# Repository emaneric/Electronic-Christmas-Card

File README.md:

# Electronic-Christmas-Card
A christmas card made from a PCB with a LED display, buttons, and buzzer.

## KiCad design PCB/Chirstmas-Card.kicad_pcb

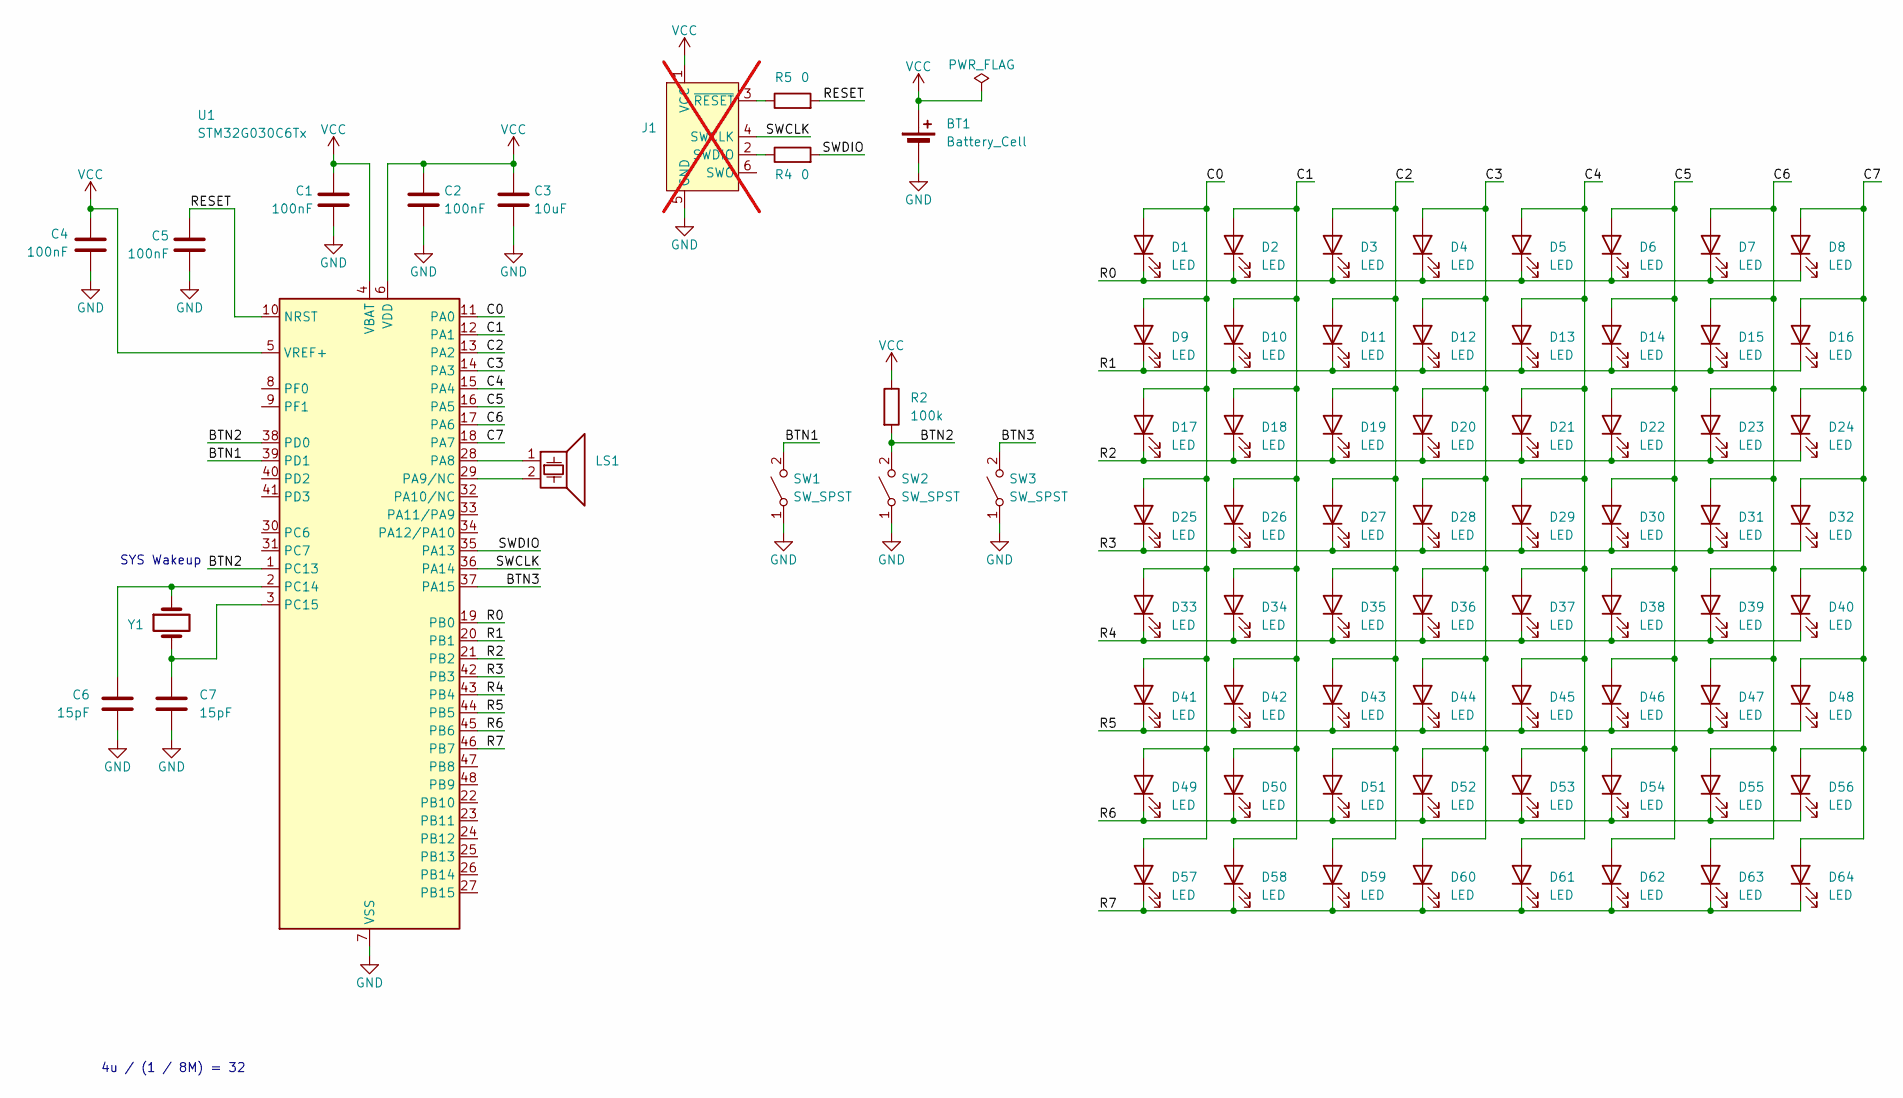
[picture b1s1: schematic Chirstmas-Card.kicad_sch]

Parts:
BT1: Battery_Cell; CR2032-BS-6-1; MPN CR2032-BS-6-1; JLC C70377
C1, C2, C4, C5: 100nF; C_0402_1005Metric; MPN CC0402KRX7R9BB104; JLC C131394
C3: 10uF; C_0603_1608Metric; MPN CL10A106MA8NRNC; JLC C96446
C6, C7: 15pF; C_0402_1005Metric; MPN 0402CG150J500NT; JLC C1548
D1, D2, D3, D4, D5, D6, D7, D8, D9, D10, D11, D12, D13, D14, D15, D16, D17, D18, D19, D20, D21, D22, D23, D24, D25, D26, D27, D28, D29, D30, D31, D32, D33, D34, D35, D36, D37, D38, D39, D40, D41, D42, D43, D44, D45, D46, D47, D48, D49, D50, D51, D52, D53, D54, D55, D56, D57, D58, D59, D60, D61, D62, D63, D64: LED; MHT151WDT; MPN MHT151WDT; JLC C401114
J1: Conn_ARM_SWD_TagConnect_TC2030-NL; Tag-Connect_TC2030-IDC-NL_2x03_P1.27mm_Vertical; not fitted
LS1: Speaker_Crystal; FUET-1230; MPN FUET-1230; JLC C391037
R2: 100k; R_0603_1608Metric; MPN 0402WGF1003TCE; JLC C25741
R4, R5: 0; R_0603_1608Metric; MPN 0402WGF1003TCE; JLC C25741
SW1, SW2, SW3: SW_SPST; KH-6X6X5H-STM; MPN KH-6X6X5H-STM; JLC C2837531
U1: STM32G030C6Tx; LQFP-48_7x7mm_P0.5mm; MPN STM32G030C6T6; JLC C529328
Y1: Crystal; Crystal_SMD_3215-2Pin_3.2x1.5mm; MPN Q13FC1350000400; JLC C32346

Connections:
/BTN1: SW1.2 (B), U1.39 (PD1)
/BTN2: R2.2, SW2.2 (B), U1.1 (PC13), U1.38 (PD0)
/BTN3: SW3.2 (B), U1.37 (PA15)
/C0: D1.2 (A), D9.2 (A), D17.2 (A), D25.2 (A), D33.2 (A), D41.2 (A), D49.2 (A), D57.2 (A), U1.11 (PA0)
/C1: D2.2 (A), D10.2 (A), D18.2 (A), D26.2 (A), D34.2 (A), D42.2 (A), D50.2 (A), D58.2 (A), U1.12 (PA1)
/C2: D3.2 (A), D11.2 (A), D19.2 (A), D27.2 (A), D35.2 (A), D43.2 (A), D51.2 (A), D59.2 (A), U1.13 (PA2)
/C3: D4.2 (A), D12.2 (A), D20.2 (A), D28.2 (A), D36.2 (A), D44.2 (A), D52.2 (A), D60.2 (A), U1.14 (PA3)
/C4: D5.2 (A), D13.2 (A), D21.2 (A), D29.2 (A), D37.2 (A), D45.2 (A), D53.2 (A), D61.2 (A), U1.15 (PA4)
/C5: D6.2 (A), D14.2 (A), D22.2 (A), D30.2 (A), D38.2 (A), D46.2 (A), D54.2 (A), D62.2 (A), U1.16 (PA5)
/C6: D7.2 (A), D15.2 (A), D23.2 (A), D31.2 (A), D39.2 (A), D47.2 (A), D55.2 (A), D63.2 (A), U1.17 (PA6)
/C7: D8.2 (A), D16.2 (A), D24.2 (A), D32.2 (A), D40.2 (A), D48.2 (A), D56.2 (A), D64.2 (A), U1.18 (PA7)
/R0: D1.1 (K), D2.1 (K), D3.1 (K), D4.1 (K), D5.1 (K), D6.1 (K), D7.1 (K), D8.1 (K), U1.19 (PB0)
/R1: D9.1 (K), D10.1 (K), D11.1 (K), D12.1 (K), D13.1 (K), D14.1 (K), D15.1 (K), D16.1 (K), U1.20 (PB1)
/R2: D17.1 (K), D18.1 (K), D19.1 (K), D20.1 (K), D21.1 (K), D22.1 (K), D23.1 (K), D24.1 (K), U1.21 (PB2)
/R3: D25.1 (K), D26.1 (K), D27.1 (K), D28.1 (K), D29.1 (K), D30.1 (K), D31.1 (K), D32.1 (K), U1.42 (PB3)
/R4: D33.1 (K), D34.1 (K), D35.1 (K), D36.1 (K), D37.1 (K), D38.1 (K), D39.1 (K), D40.1 (K), U1.43 (PB4)
/R5: D41.1 (K), D42.1 (K), D43.1 (K), D44.1 (K), D45.1 (K), D46.1 (K), D47.1 (K), D48.1 (K), U1.44 (PB5)
/R6: D49.1 (K), D50.1 (K), D51.1 (K), D52.1 (K), D53.1 (K), D54.1 (K), D55.1 (K), D56.1 (K), U1.45 (PB6)
/R7: D57.1 (K), D58.1 (K), D59.1 (K), D60.1 (K), D61.1 (K), D62.1 (K), D63.1 (K), D64.1 (K), U1.46 (PB7)
/RESET: C5.1, R5.2, U1.10 (NRST)
/SWCLK: J1.4 (SWCLK), U1.36 (PA14)
/SWDIO: R4.2, U1.35 (PA13)
GND: BT1.2 (-), C1.2, C2.2, C3.2, C4.2, C5.2, C6.2, C7.2, J1.5 (GND), SW1.1 (A), SW2.1 (A), SW3.1 (A), U1.7 (VSS)
unnamed: J1.2 (SWDIO), R4.1
unnamed: J1.3 (~RESET), R5.1
unnamed: LS1.1, U1.28 (PA8)
unnamed: LS1.2, U1.29 (PA9/NC)
unnamed: C6.1, U1.2 (PC14), Y1.1
unnamed: C7.1, U1.3 (PC15), Y1.2
VCC: BT1.1 (+), C1.1, C2.1, C3.1, C4.1, J1.1 (VCC), R2.1, U1.4 (VBAT), U1.5 (VREF+), U1.6 (VDD)

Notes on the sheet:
SYS Wakeup
4u / (1 / 8M) = 32

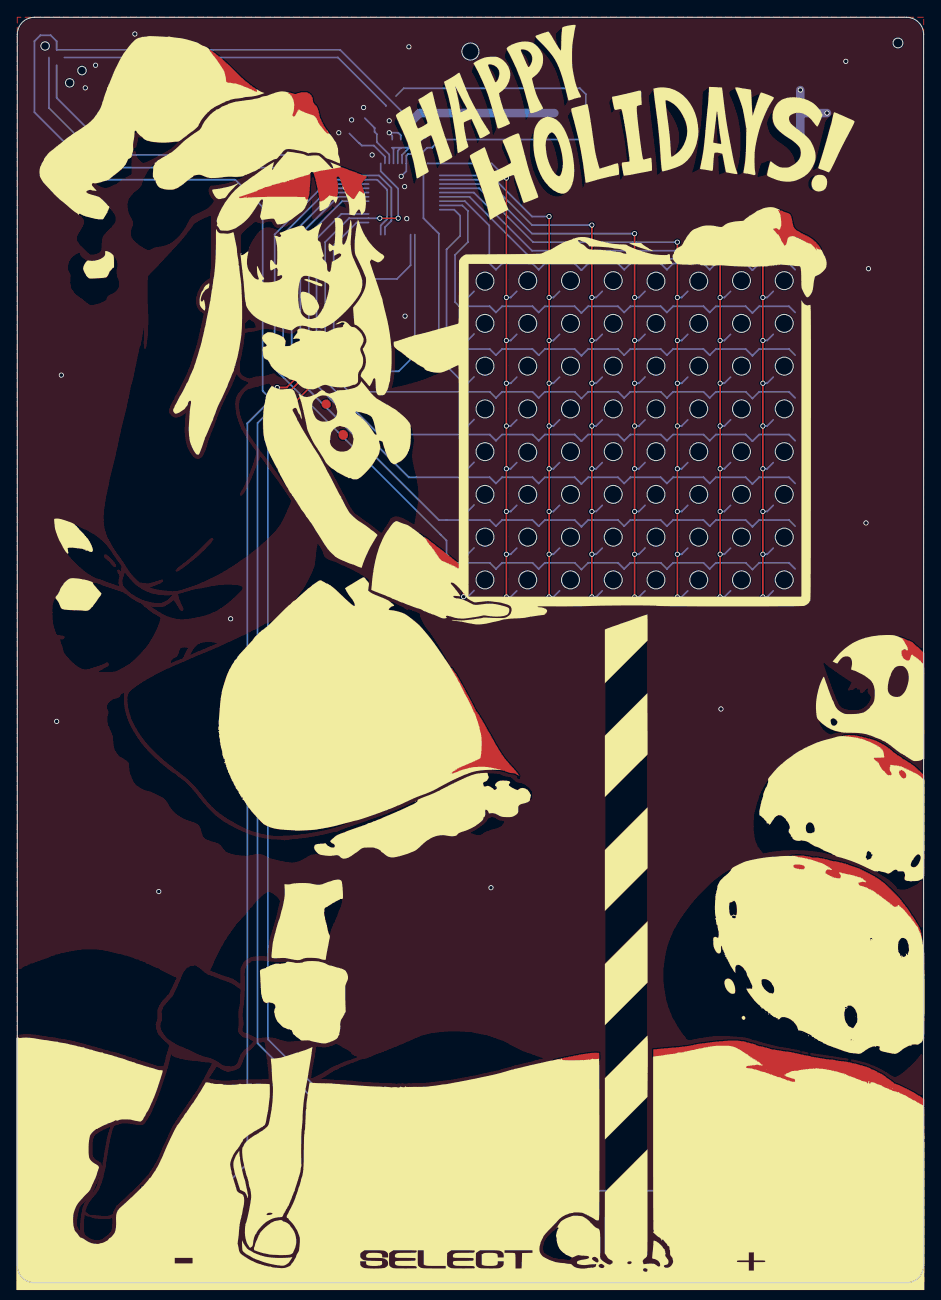
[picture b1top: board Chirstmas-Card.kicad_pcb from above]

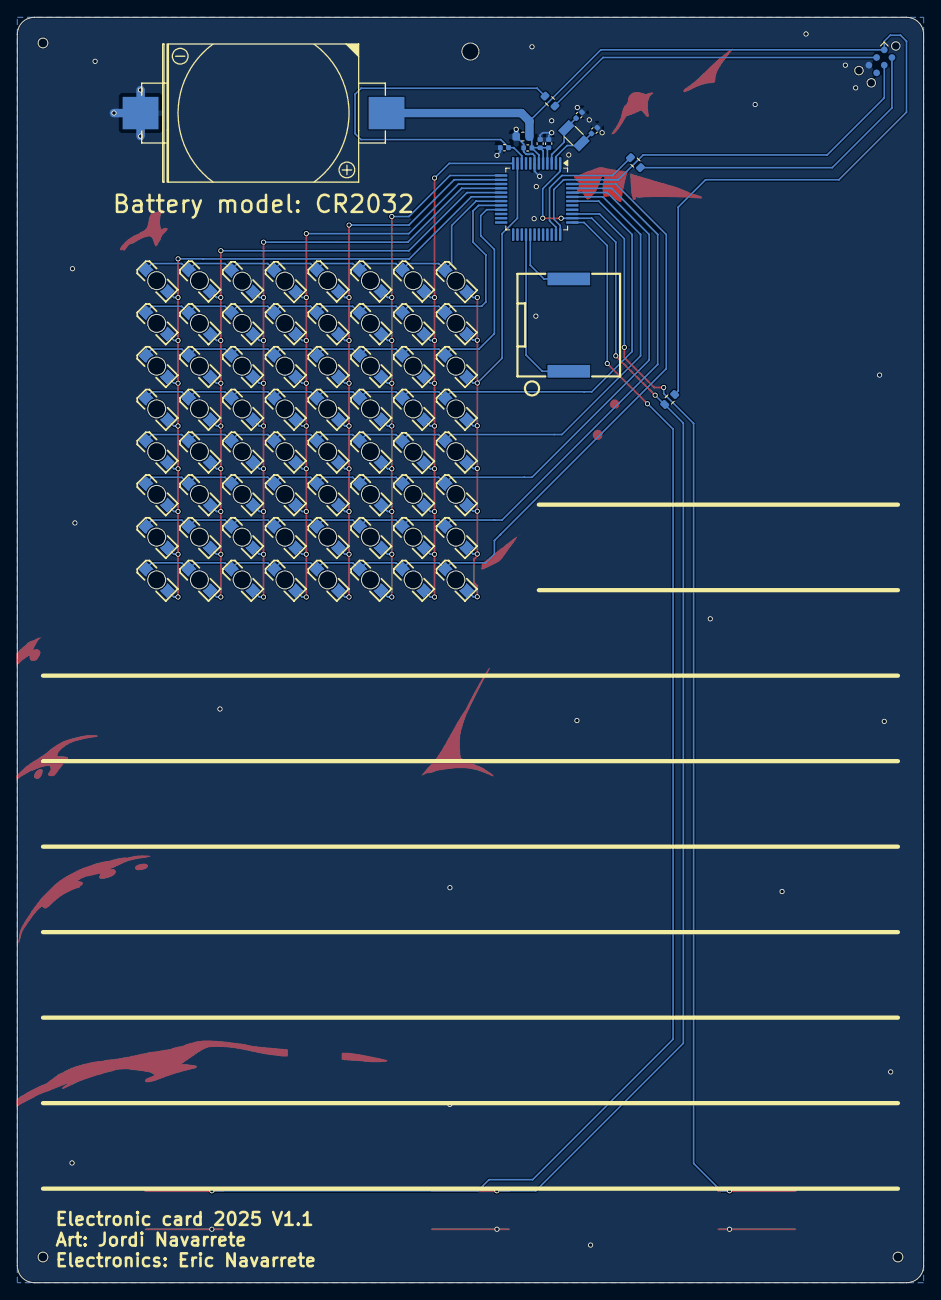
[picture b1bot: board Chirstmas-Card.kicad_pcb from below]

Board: 2 copper layers, 106.0 x 148.0 mm, 83 parts (79 on the bottom side), 30 nets.

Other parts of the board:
Art: Val**; jordi-christmas-girl-V2

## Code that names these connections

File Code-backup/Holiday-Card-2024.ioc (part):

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Mcu.Name=STM32G030C(6-8)Tx
Mcu.Package=LQFP48
Mcu.UserName=STM32G030C6Tx
PA0.GPIOParameters=GPIO_Speed,GPIO_Label
PA0.GPIO_Label=C0
PA0.GPIO_Speed=GPIO_SPEED_FREQ_LOW
PA0.Signal=GPIO_Output
PA1.GPIOParameters=GPIO_Speed,GPIO_Label
PA1.GPIO_Label=C1
PA1.GPIO_Speed=GPIO_SPEED_FREQ_LOW
PA1.Signal=GPIO_Output
PA13.Mode=Serial_Wire
PA13.Signal=SYS_SWDIO
PA14-BOOT0.Mode=Serial_Wire
PA14-BOOT0.Signal=SYS_SWCLK
PA15.GPIOParameters=GPIO_Label
PA15.GPIO_Label=BTN3
PA15.Signal=GPIO_Input
PA2.GPIOParameters=GPIO_Speed,GPIO_Label
PA2.GPIO_Label=C2
PA2.GPIO_Speed=GPIO_SPEED_FREQ_LOW
PA2.Signal=GPIO_Output
PA3.GPIOParameters=GPIO_Speed,GPIO_Label
PA3.GPIO_Label=C3
PA3.GPIO_Speed=GPIO_SPEED_FREQ_LOW
PA3.Signal=GPIO_Output
PA4.GPIOParameters=GPIO_Speed,GPIO_Label
PA4.GPIO_Label=C4
PA4.GPIO_Speed=GPIO_SPEED_FREQ_LOW
PA4.Signal=GPIO_Output
PA5.GPIOParameters=GPIO_Speed,GPIO_Label
PA5.GPIO_Label=C5
PA5.GPIO_Speed=GPIO_SPEED_FREQ_LOW
PA5.Signal=GPIO_Output
PA6.GPIOParameters=GPIO_Speed,GPIO_Label
PA6.GPIO_Label=C6
PA6.GPIO_Speed=GPIO_SPEED_FREQ_LOW
PA6.Signal=GPIO_Output
PA7.GPIOParameters=GPIO_Speed,GPIO_Label
PA7.GPIO_Label=C7
PA7.GPIO_Speed=GPIO_SPEED_FREQ_LOW
PA7.Signal=GPIO_Output
PA8.Signal=S_TIM1_CH1
PA9.Signal=S_TIM1_CH2
PB0.GPIOParameters=GPIO_Speed,GPIO_Label
PB0.GPIO_Label=R0
PB0.GPIO_Speed=GPIO_SPEED_FREQ_LOW
PB0.Signal=GPIO_Output
PB1.GPIOParameters=GPIO_Speed,GPIO_Label
PB1.GPIO_Label=R1
PB1.GPIO_Speed=GPIO_SPEED_FREQ_LOW
PB1.Signal=GPIO_Output
PB2.GPIOParameters=GPIO_Speed,GPIO_Label
PB2.GPIO_Label=R2
PB2.GPIO_Speed=GPIO_SPEED_FREQ_LOW
PB2.Signal=GPIO_Output
PB3.GPIOParameters=GPIO_Speed,GPIO_Label
PB3.GPIO_Label=R3
PB3.GPIO_Speed=GPIO_SPEED_FREQ_LOW
PB3.Signal=GPIO_Output
PB4.GPIOParameters=GPIO_Speed,GPIO_Label
PB4.GPIO_Label=R4
PB4.GPIO_Speed=GPIO_SPEED_FREQ_LOW
PB4.Signal=GPIO_Output
PB5.GPIOParameters=GPIO_Speed,GPIO_Label
PB5.GPIO_Label=R5
PB5.GPIO_Speed=GPIO_SPEED_FREQ_LOW
PB5.Signal=GPIO_Output
PB6.GPIOParameters=GPIO_Speed,GPIO_Label
PB6.GPIO_Label=R6
PB6.GPIO_Speed=GPIO_SPEED_FREQ_LOW
PB6.Signal=GPIO_Output
PB7.GPIOParameters=GPIO_Speed,GPIO_Label
PB7.GPIO_Label=R7
PB7.GPIO_Speed=GPIO_SPEED_FREQ_LOW
PB7.Signal=GPIO_Output
PC13.Mode=SYS_WakeUp1
PC13.Signal=SYS_WKUP2
PC14-OSC32_IN\ (PC14).Mode=LSE-External-Oscillator
PC14-OSC32_IN\ (PC14).Signal=RCC_OSC32_IN
PC15-OSC32_OUT\ (PC15).Mode=LSE-External-Oscillator
PC15-OSC32_OUT\ (PC15).Signal=RCC_OSC32_OUT
PD0.GPIOParameters=GPIO_Label
PD0.GPIO_Label=BTN2
PD0.Signal=GPIO_Input
PD1.GPIOParameters=GPIO_Label
PD1.GPIO_Label=BTN1
PD1.Signal=GPIO_Input
RCC.HSE_VALUE=8000000
RCC.SYSCLKFreq_VALUE=48000000
RCC.SYSCLKSource=RCC_SYSCLKSOURCE_PLLCLK
board=custom

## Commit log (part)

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2024-11-03 Initial Commit, work in progress
2024-12-12 Added initial buzzer functionality
2024-12-14 -Working on adding melody functionality
2024-12-19 WIP. Working on display functionality
2026-01-01 -migration to new cube mx version and cmake toolchain
2026-01-01 -got code working in vscode
2026-01-01 -modified timer values to give a 60fps framerate
2026-01-16 -Unsuccesful attempt to trigger DMA transfer from timer
2026-01-24 Generated minimal code from cube mx
2026-01-24 -removing hal parts of code
